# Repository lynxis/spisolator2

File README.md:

# spisolator2

A pcb to switch the SPI flashchip between a flasher and a mainboard.

A useful part for coreboot development.

Based on the [spisolator from urjaman]( https://github.com/urjaman/spisolator).

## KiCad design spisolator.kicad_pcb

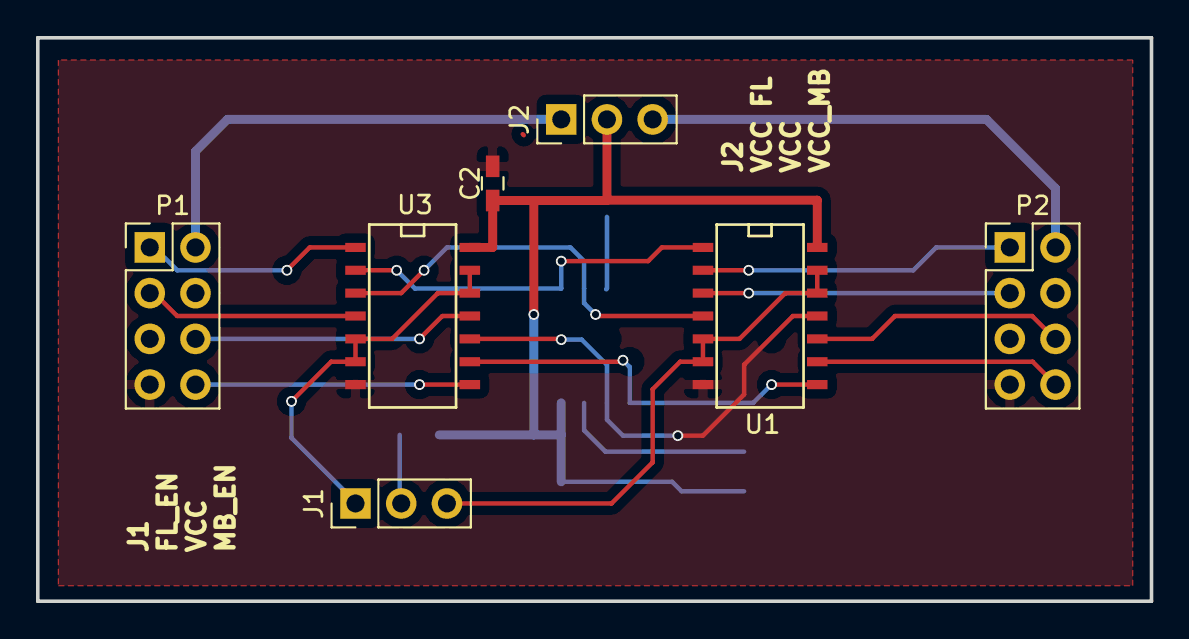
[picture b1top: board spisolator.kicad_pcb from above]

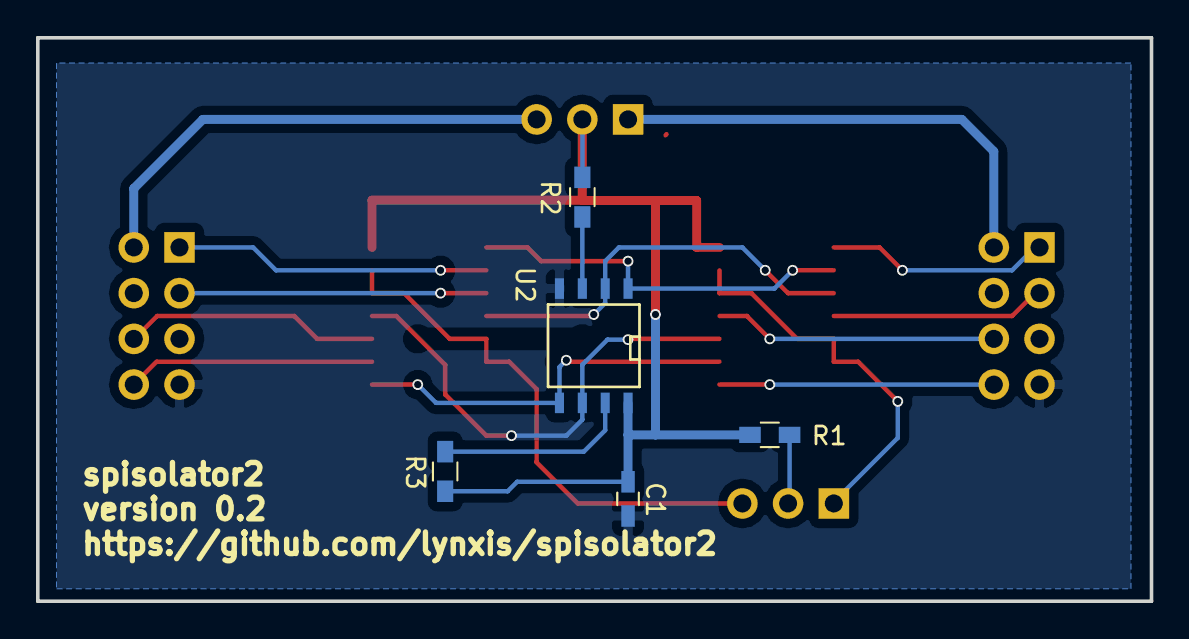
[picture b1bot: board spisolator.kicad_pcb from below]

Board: 2 copper layers, 61.9 x 31.3 mm, 12 parts (5 on the bottom side), 21 nets.

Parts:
C1: 10nF; C_0603_HandSoldering
C2: 10uF; C_0603_HandSoldering
J1, J2: Conn_01x03_Male; Pin_Header_Straight_1x03_Pitch2.54mm
P1, P2: CONN_02X04; Pin_Header_Straight_2x04_Pitch2.54mm
R1, R2, R3: 10k; R_0603_HandSoldering
U1, U3: 4066; SOIC-14_N
U2: 25LXX; SOIC-8-N

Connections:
+3V3: C1.1, C2.1, J2.2, R1.1, R2.2, R3.1, U1.14, U2.8, U3.14
/CLK: U1.11, U2.6, U3.10
/CLK_FL: P1.6, U3.11
/CLK_MB: P2.6, U1.10
/EN_FL: J1.1, U3.5, U3.6, U3.12, U3.13
/EN_MB: J1.3, U1.5, U1.6, U1.12, U1.13
/SI: U1.8, U2.5, U3.9
/SI_FL: P1.3, U3.4
/SI_MB: P2.8, U1.9
/SO: U1.4, U2.2, U3.3
/SO_FL: P1.8, U3.8
/SO_MB: P2.3, U1.3
/~CS: U1.1, U2.1, U3.2
/~CS_FL: P1.1, U3.1
/~CS_MB: P2.1, U1.2
/~WP: R2.1, U2.3
GND: C1.2, C2.2, P1.7, P2.7, U1.7, U2.4, U3.7
unnamed: J1.2, R1.2
unnamed: R3.2, U2.7
VCC_Flasher: J2.1, P1.2
VCC_Mainboard: J2.3, P2.2

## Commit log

2018-06-01 initial
2018-06-01 assosiate footprints
2018-06-01 annotate schematics
2018-06-01 pcb: started over the wiring
2018-06-01 pcb: reduced the board
2018-06-01 add README and LICENSE
2018-06-01 schematics: add net annotations, correct logicbuffer, ...
2018-06-01 add netlist
2018-06-01 add pcb
2018-06-01 README: correct headline
2018-06-02 pcb: remove some 90o corners
